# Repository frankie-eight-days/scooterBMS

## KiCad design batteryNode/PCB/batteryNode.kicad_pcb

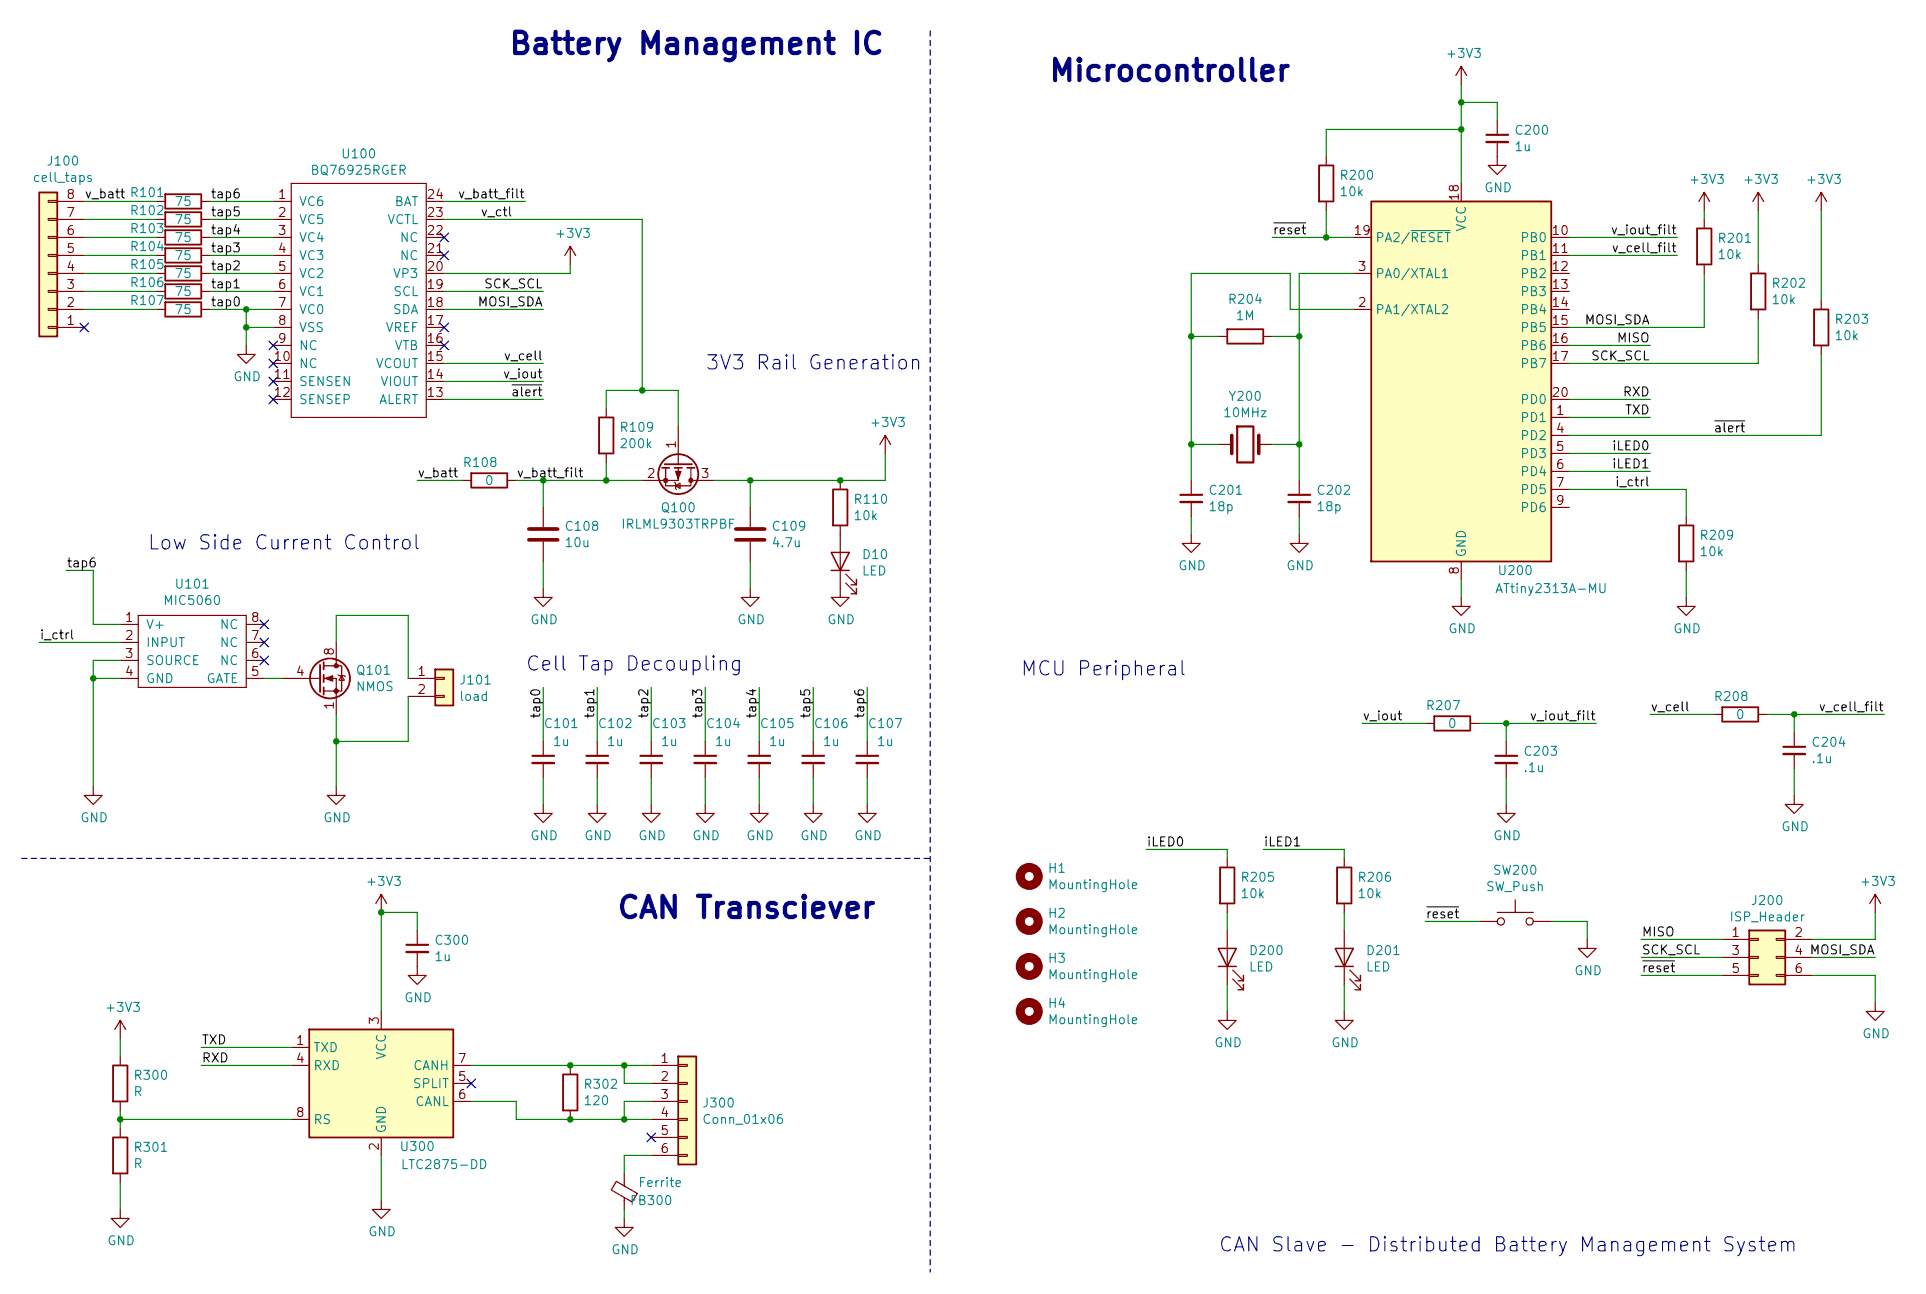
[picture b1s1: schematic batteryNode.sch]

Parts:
C101, C102, C103, C104, C105, C106, C107, C200, C300: 1u; C_0603_1608Metric
C108: 10u; C_0603_1608Metric_Pad1.05x0.95mm_HandSolder
C109: 4.7u; C_0603_1608Metric_Pad1.05x0.95mm_HandSolder
C201, C202: 18p; C_0402_1005Metric
C203, C204: .1u; C_0603_1608Metric
D10, D200, D201: LED; LED_0603_1608Metric
FB300: Ferrite; L_0603_1608Metric
H1, H2, H3, H4: MountingHole; MountingHole_3.2mm_M3_Pad_Via
J100: cell_taps; Molex_Mini-Fit_Jr_5569-08A2_2x04_P4.20mm_Horizontal
J101: load; Molex_Mini-Fit_Jr_5569-02A2_2x01_P4.20mm_Horizontal
J200: ISP_Header; PinHeader_2x03_P1.27mm_Vertical
J300: Conn_01x06; Molex_Mini-Fit_Jr_5569-06A2_2x03_P4.20mm_Horizontal
Q100: IRLML9303TRPBF; SOT-23
Q101: NMOS; PowerPAK_SO-8_Single
R101, R102, R103, R104, R105, R106, R107: 75; R_0805_2012Metric
R108, R207, R208: 0; R_0603_1608Metric
R109: 200k; R_0603_1608Metric
R110, R200, R201, R202, R203, R205, R206, R209: 10k; R_0603_1608Metric
R204: 1M; C_0603_1608Metric
R300, R301: R; R_0603_1608Metric
R302: 120; R_0603_1608Metric
SW200: SW_Push; SW_SPST_EVQPE1
U100: BQ76925RGER; VQFN-24-1EP_4x4mm_P0.5mm_EP2.45x2.45mm_ThermalVias
U101: MIC5060; MLF-8-1EP_3x3mm_P0.65mm_EP1.55x2.3mm
U200: ATtiny2313A-MU; MLF-20-1EP_4x4mm_P0.5mm_EP2.6x2.6mm
U300: LTC2875-DD; DFN-8-1EP_3x3mm_P0.5mm_EP1.66x2.38mm
Y200: 10MHz; ECS-100-18-23G-JGN-TR

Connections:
+3V3: C109.1, C200.1, C300.1, J200.2, Q100.3 (D), R110.1, R200.1, R201.1, R202.1, R203.1, R300.1, U100.20 (VP3), U200.18 (VCC), U300.3 (VCC)
/MISO: J200.1, U200.16 (PB6)
/MOSI_SDA: J200.4, R201.2, U100.18 (SDA), U200.15 (PB5)
/RXD: U200.20 (PD0), U300.4 (RXD)
/SCK_SCL: J200.3, R202.2, U100.19 (SCL), U200.17 (PB7)
/TXD: U200.1 (PD1), U300.1 (TXD)
/iLED0: R205.1, U200.5 (PD3)
/iLED1: R206.1, U200.6 (PD4)
/i_ctrl: R209.1, U101.2 (INPUT), U200.7 (PD5)
/tap1: C102.1, R106.1, U100.6 (VC1)
/tap2: C103.1, R105.1, U100.5 (VC2)
/tap3: C104.1, R104.1, U100.4 (VC3)
/tap4: C105.1, R103.1, U100.3 (VC4)
/tap5: C106.1, R102.1, U100.2 (VC5)
/tap6: C107.1, R101.1, U100.1 (VC6), U101.1 (V+)
/v_batt: J100.8, R101.2, R108.2
/v_batt_filt: C108.1, Q100.2 (S), R108.1, R109.2, U100.24 (BAT)
/v_cell: R208.2, U100.15 (VCOUT)
/v_cell_filt: C204.1, R208.1, U200.11 (PB1)
/v_ctl: Q100.1 (G), R109.1, U100.23 (VCTL)
/v_iout: R207.2, U100.14 (VIOUT)
/v_iout_filt: C203.1, R207.1, U200.10 (PB0)
/~alert: R203.2, U100.13 (ALERT), U200.4 (PD2)
/~reset: J200.5, R200.2, SW200.1, U200.19 (PA2/~RESET)
GND: C101.1, C101.2, C102.2, C103.2, C104.2, C105.2, C106.2, C107.2, C108.2, C109.2, C200.2, C201.2, C202.2, C203.2, C204.2, C300.2, D10.1 (K), D200.1 (K), D201.1 (K), FB300.1, J101.2, J200.6, Q101.1 (S), R107.1, R209.2, R301.2, SW200.2, U100.7 (VC0), U100.8 (VSS), U101.3 (SOURCE), U101.4 (GND), U200.8 (GND), U200.21 (GND), U300.2 (GND), U300.9 (GND)
unnamed: C201.1, R204.2, U200.2 (PA1/XTAL2), Y200.1
unnamed: C202.1, R204.1, U200.3 (PA0/XTAL1), Y200.2
unnamed: D10.2 (A), R110.2
unnamed: D200.2 (A), R205.2
unnamed: D201.2 (A), R206.2
unnamed: FB300.2, J300.6
unnamed: J100.2, R107.2
unnamed: J100.3, R106.2
unnamed: J100.4, R105.2
unnamed: J100.5, R104.2
unnamed: J100.6, R103.2
unnamed: J100.7, R102.2
unnamed: J101.1, Q101.8 (D)
unnamed: J300.1, J300.2, R302.1, U300.7 (CANH)
unnamed: J300.3, J300.4, R302.2, U300.6 (CANL)
unnamed: Q101.4 (G), U101.5 (GATE)
unnamed: R300.2, R301.1, U300.8 (RS)

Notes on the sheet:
Microcontroller
CAN Transciever
MCU Peripheral
Cell Tap Decoupling
Battery Management IC
3V3 Rail Generation
CAN Slave - Distributed Battery Management System
Low Side Current Control

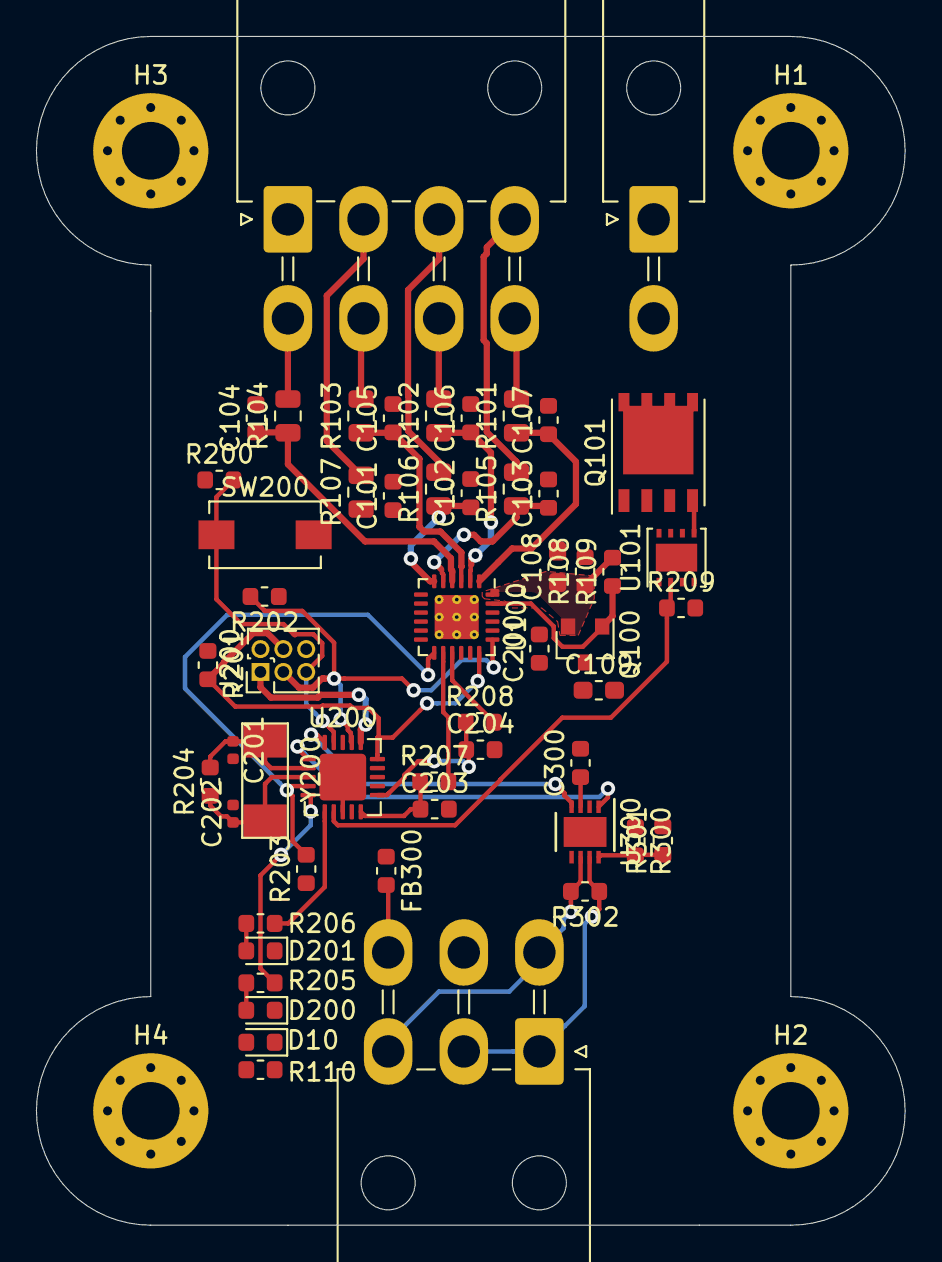
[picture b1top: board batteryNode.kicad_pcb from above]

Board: 2 copper layers, 48.3 x 66.0 mm, 58 parts (0 on the bottom side), 41 nets.

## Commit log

2019-06-21 Inital Schematic Creating
    Rough idea of what BMS IC and MCU look like.
2019-06-21 updatedSchem
    changes some more small things
2019-06-21 modified schem
2019-06-25 Added some footprints and digikey part numbers
2019-06-27 Schematic Complete
    V 0.1 of schematic complete. Trial layout next
2019-06-27 Terrible First Version Layout
    First version layout. Going to try some routing with this and see how it works out.
2019-06-28 Made some small changes
2019-06-28 Restarted Layout and added logos and mounting holes to schematic
2019-07-03 added current control. Started V2 of layout
2019-07-03 finished v2 layout and V1 of edge cuts. edges too big around mounting holes
2019-08-20 Old changes made that I can't remember
    Hopefully I don't have to roll the project back :)
